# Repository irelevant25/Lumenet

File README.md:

# Lumenet

A lighting desk in the browser, in the old style with faders, and **dmxbox**: a small box that takes what the
desk sends over USB to the DMX512 cable of the lights.

## What it does

* **Faders for 1 to 8 universes** of 512 channels, a page at a time, and **128 memories**: looks stored from the
  faders, each with a fader of its own. Keys under the faders, independents at the side, a master, blackout,
  solo up and down, and a rate for everything that runs.
* **Several boxes at once**, each output playing a universe: by themselves, or as the project says. Besides
  the box, **Art-Net** nodes, **sACN** and DMX USB interfaces of the kind of the **Enttec DMX USB Pro** play the
  universes as well.
* **Sequences**, made by hand or from a template (chase, wave, strobe, fire, storm), and a **stack**: the cues
  of a show with their fades and waits, played one after the other with GO, or at moments of the music;
  a cue sheet to print.
* **Effects** worked out live from a shape: circles and swings of moving heads, chases and pulses, rainbows
  and color chases, and patterns over the cells of LED bars by where they are on the stage. Each has a key and
  a fader, live speed, size and spread, and a preview; on Main and in the stack too.
* **Sounds:** music and other sounds from files, mixed by the desk program and played on a sound device of the
  PC, each with a key and a fader, its own level in decibels, fades, pan, speed, pitch, echo and reverb; a
  volume for all, MUTE and LISTEN on a second device; in the stack and in sequences, where a sound can play on
  through the steps after it until its end or a release. Beside them the tracks of the USB stick of a
  Soundcraft Ui mixer, played on the mixer's own player, its PLAYER channel the volume of all sounds and MUTE,
  both ways; the desk finds the mixer in the network by itself.
* **Fixtures:** lights by their kind, taken from the Open Fixture Library (666 lights) or the library of QLC+
  (1,781), played by intensity and color, moving heads by pan and tilt too; groups with one fader for all their
  lights.
* **Stage:** a plan of the rig with every light in its live color, a strobe flashing too.
* **Projects** in files, with notes for the show, undo and redo, an autosave, and backups into a folder that
  Google Drive, OneDrive or Dropbox syncs; export and import as one ZIP, and import of the show files of
  theatre consoles (USITT ASCII).
* **Phones and tablets** in the same network can use the desk as well, with a password.
* **MIDI controllers** play the desk: their keys press its keys, their faders and knobs move its faders, and
  the desk lights their keys and moves their motorized faders. Learn maps a control in two presses; the Akai
  APC mini mk2, Korg nanoKONTROL2 and Behringer X-Touch Mini and Compact have ready-made mappings. Other
  programs such as QLab and TouchOSC work the same keys and faders with **OSC**.
* A keyboard shortcut for every key, the usual ones from the start, and settings for how each device shows
  the desk, with a setup by the kind of show on the first start.
* **Ten example shows** to start from, from a few looks and cues to a whole concert, one of effects, two of
  sounds and one whose cues come on the music.

The desk also works without the box, on other DMX hardware or none. The box speaks Art-Net too, so other
lighting software such as QLC+ can use it.

## What it runs on

**The desk** runs on Windows 10 and 11 (64-bit), and its page in a current browser. With LAN switched on in
the page, phones and tablets in the same network can use it too: they get the same page, laid out for their
screen, and get in with a password.

**The boxes:** four dmxboxes bring the desk to DMX. Each is a USB network adapter for the computer, which
Windows, macOS and Linux take without a driver, and the desk finds it by itself. One USB cable powers it and
carries the data.

| | <br>[**Box 1**](boxes/box1/README.md)<br>Pico | <br>[**Box 2**](boxes/box2/README.md)<br>PIC32 | <br>[**Box 3**](boxes/box3/README.md)<br>RP2040 | <br>[**Box 4**](boxes/box4/README.md)<br>RP2040 |
|---|:---:|:---:|:---:|:---:|
| Isolated DMX output | ✅ | ✅ | ✅ | ✅ |
| RDM: sets up the lights | ✅ | ✅ | ✅ | ✅ |
| Number switch, for several boxes | ✅ | ✅ | ✅ | ✅ |
| USB-C | ❌ | ✅ | ✅ | ✅ |
| DMX IN: a console plays the desk | ❌ | ❌ | ❌ | ✅ |
| MIDI IN and OUT | ❌ | ❌ | ❌ | ✅ |
| USB OUT to the next box | ❌ | ❌ | ❌ | ✅ |
| POWER socket for a charger | ❌ | ❌ | ❌ | ✅ |
| Update firmware over USB | ✅ | ❌ | ✅ | ✅ |
| Assembly | THT | THT | SMD | SMD |
| Soldered by external company | ❌ | ❌ | ✅ | ✅ |
| Case | 3D printed | 3D printed | 3D printed | Aluminium or 3D printed |

The pictures are renders of the designs; none of the four has been built yet. The first box 1, a
Raspberry Pi Pico on a perfboard, was built and works with the desk.

## Get it

**Download:** `Lumenet.exe` from the newest release on the [Releases](../../releases) page. It is the whole desk in
one file, with nothing to install. Start it: the page opens in the browser, and Lumenet sits in the
notification area of the taskbar, where its menu opens the page again, shows the log, and ends it. Windows may
say that it does not know the program, as it is not signed: More info, then Run anyway. Later versions come
from the desk itself: Settings, About, says when one is out and puts it in place at a press.

**From the sources:** with the .NET 10 SDK and Node.js 22, `run.cmd` starts the desk; then open
http://localhost:4200. `sim.cmd` starts a simulated box, Art-Net node, sACN receiver or USB interface for the
desk to play on, or a MIDI controller to play it with, without the hardware (see
[DEV.md](DEV.md#simulated-devices-simcmd)).

**A box:** what to order and what to buy and fit yourself is in each box's BOM.md, for example
[box 4's](boxes/box4/BOM.md); the schematics, the boards and the firmware are in [DEV.md](DEV.md#1-hardware), and
all four boxes in [boxes/](boxes/README.md).

## More

* [MANUAL.md](MANUAL.md): every view, key and setting of the desk.
* [DEV.md](DEV.md): the box's hardware and firmware, the PC side, how the desk is built and tested, the DX
  protocol, and what has been tried so far.

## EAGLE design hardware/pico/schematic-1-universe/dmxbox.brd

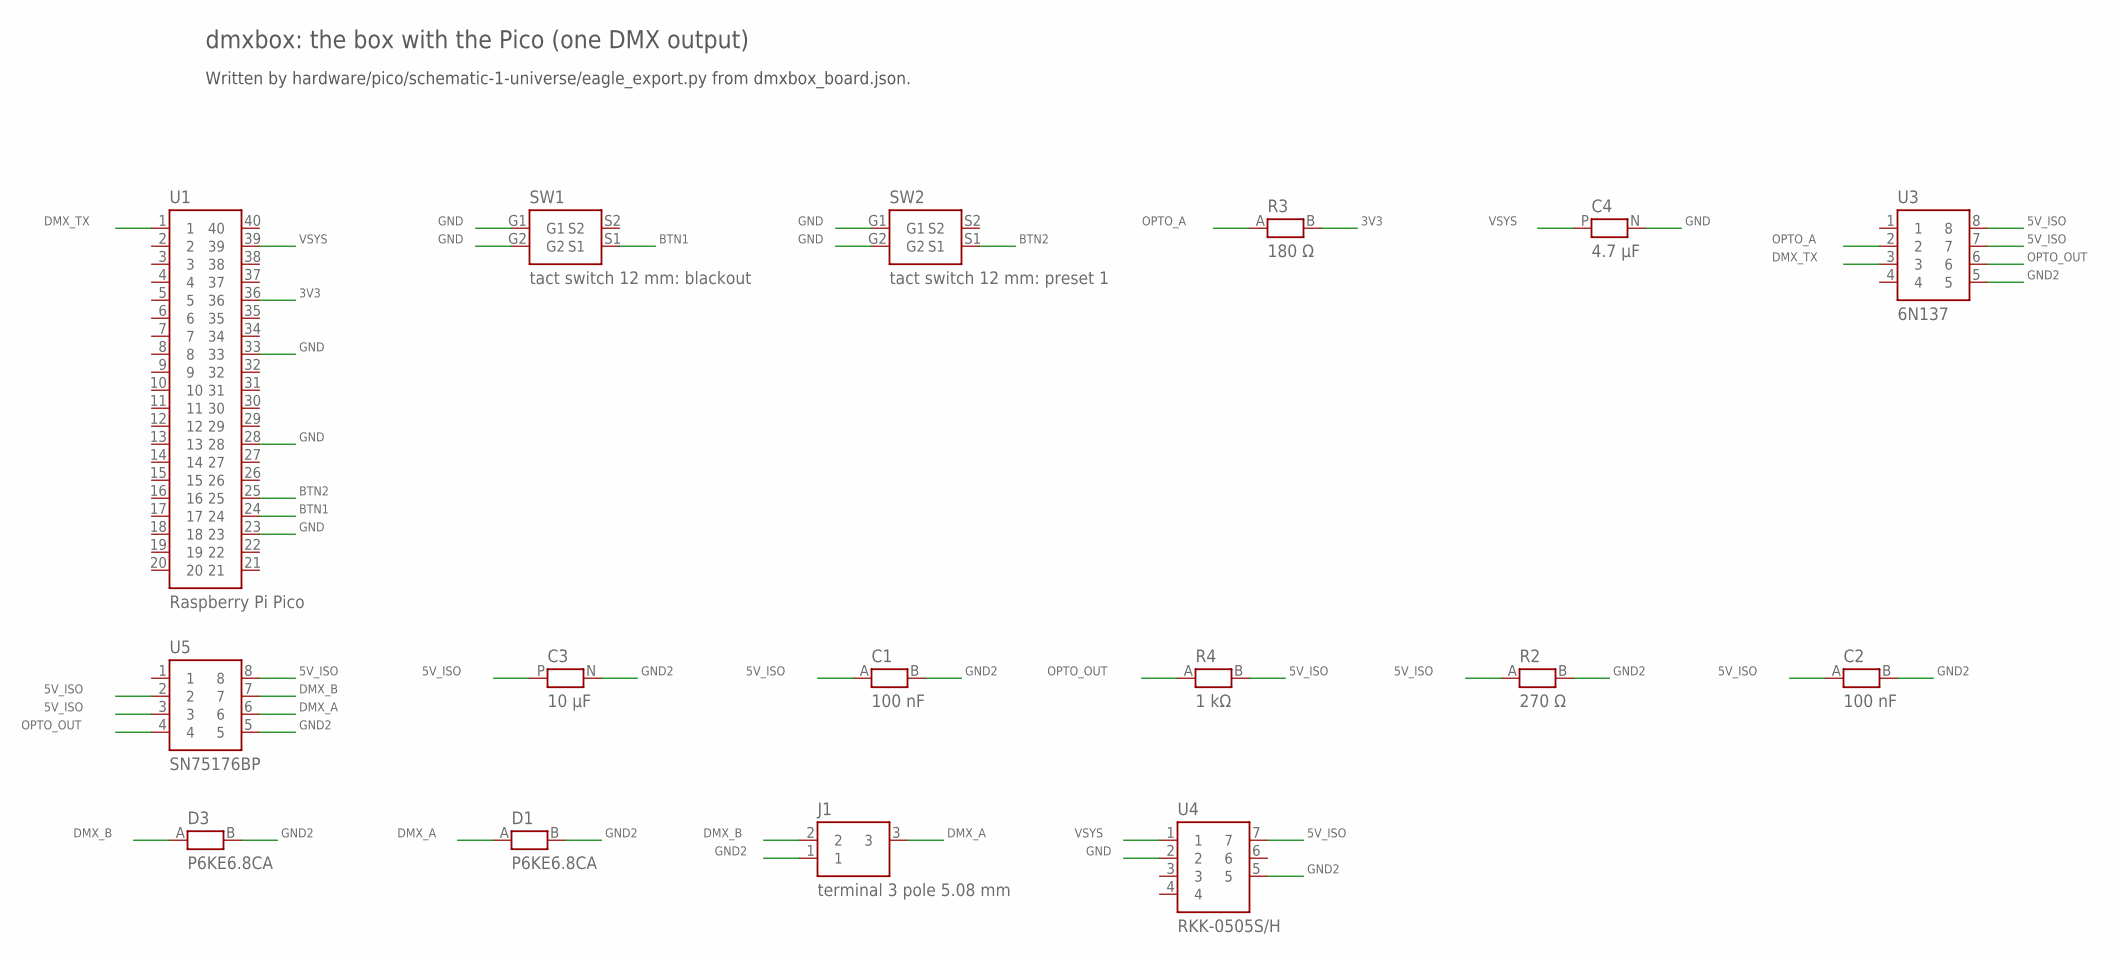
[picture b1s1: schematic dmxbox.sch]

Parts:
C1, C2: 100 nF; C_5.00
C3: 10 µF; CP_2.00
C4: 4.7 µF; CP_2.00
D1, D3: P6KE6.8CA; DO15_10.16
J1: terminal 3 pole 5.08 mm; TERMINAL_3
R2: 270 Ω; R_10.16
R3: 180 Ω; R_10.16
R4: 1 kΩ; R_10.16
SW1: tact switch 12 mm: blackout; BUTTON_12MM
SW2: tact switch 12 mm: preset 1; BUTTON_12MM
U1: Raspberry Pi Pico; PICO
U3: 6N137
U4: RKK-0505S/H; RKK_SIP7
U5: SN75176BP; SN75176

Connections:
3V3: R3.B, U1.36
5V_ISO: C1.A, C2.A, C3.P, R2.A, R4.B, U3.7, U3.8, U4.7, U5.2, U5.3, U5.8
BTN1: SW1.S1, U1.24
BTN2: SW2.S1, U1.25
DMX_A: D1.A, J1.3, U5.6
DMX_B: D3.A, J1.2, U5.7
DMX_TX: U1.1, U3.3
GND: C4.N, SW1.G1, SW1.G2, SW2.G1, SW2.G2, U1.23, U1.28, U1.33, U4.2
GND2: C1.B, C2.B, C3.N, D1.B, D3.B, J1.1, R2.B, U3.5, U4.5, U5.5
OPTO_A: R3.A, U3.2
OPTO_OUT: R4.A, U3.6, U5.4
VSYS: C4.P, U1.39, U4.1

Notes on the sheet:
dmxbox: the box with the Pico (one DMX output)
Written by hardware/pico/schematic-1-universe/eagle_export.py from dmxbox_board.json.

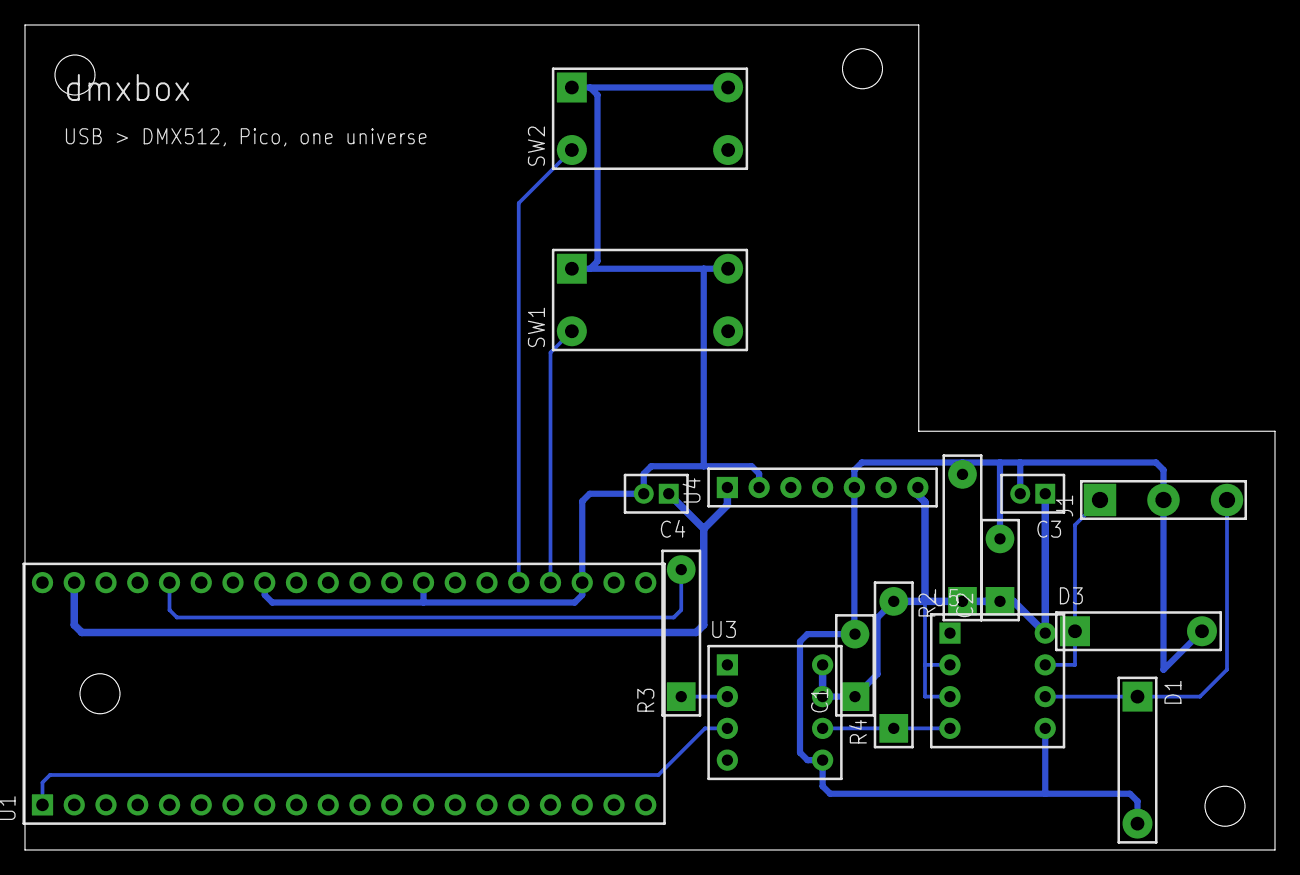
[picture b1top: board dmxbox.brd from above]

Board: 1 copper layer, 100.0 x 66.0 mm, 16 parts (0 on the bottom side), 12 nets.

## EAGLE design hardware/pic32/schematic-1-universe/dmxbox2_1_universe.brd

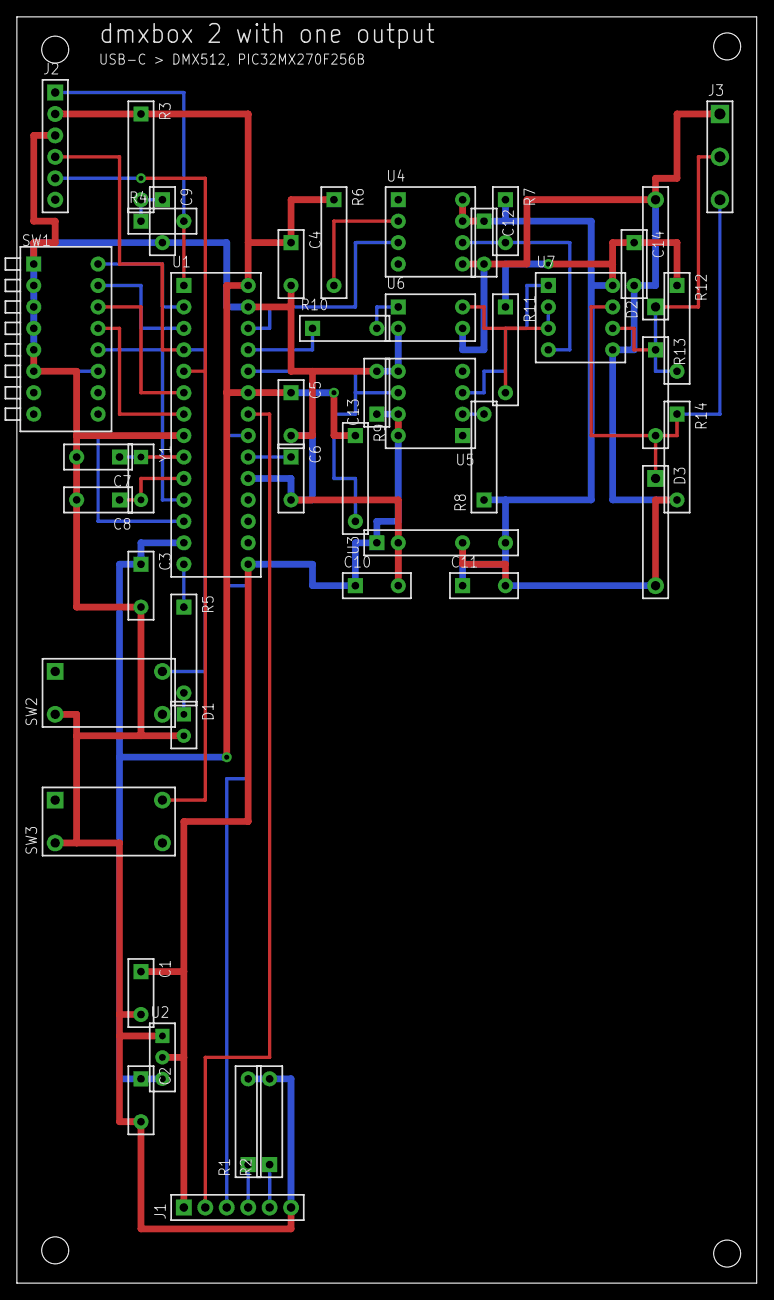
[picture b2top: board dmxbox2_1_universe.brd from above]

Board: 2 copper layers, 87.6 x 150.0 mm, 45 parts (0 on the bottom side), 35 nets.

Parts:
C1, C2, C6, C10, C11: 10 µF; C_5.08
C3, C4, C5, C9, C12, C13, C14: 100 nF; C_5.08
C7, C8: 22 pF; C_5.08
D1: LED 3 mm; LED_3MM
D2, D3: P6KE6.8CA; DO15_12.70
J1: USB 2.0 Type-C breakout; USB_C_BREAKOUT_1X6
J2: pin header 1x6; HEADER_1X6
J3: XLR 3-pin female, panel; TERMINAL_3_5.08
R1, R2: 5.1 kΩ; R_10.16
R3, R11: 10 kΩ; R_10.16
R4, R7: 1 kΩ; R_5.08_STANDING
R5: 470 Ω; R_10.16
R6: 180 Ω; R_10.16
R8: 390 Ω; R_10.16
R9: 1 kΩ; R_10.16
R10: 470 Ω; R_7.62
R12, R14: 560 Ω; R_10.16
R13: 130 Ω; R_10.16
SW1: piano DIP switch, 8 positions (DPL08RGT); PIANO_DIP_SWITCH_8
SW2, SW3: tact switch 12 x 12 mm; BUTTON_12MM
U1: PIC32MX270F256B-I/SP; PIC32MX270F256B_DIP28
U2: MCP1700-3302E/TO; MCP1700_TO92
U3: RKK-0505S/H; RKK0505SH_SIP7
U4, U5: 6N137; 6N137_DIP8
U6: PC817; PC817_DIP4
U7: MAX485; MAX485_DIP8
Y1: 8 MHz; HC49_CRYSTAL

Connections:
+3V3: C2.1, C3.1, C4.1, C5.1, J2.2, R3.1, R6.1, R9.1, U1.13, U1.23, U1.28, U2.3
+5V: C1.1, C10.1, C13.1, J1.VBUS, U1.15, U2.2, U3.1, U5.7, U5.8
+5V_ISO: C11.1, C12.1, C14.1, R7.1, R8.1, R11.1, R12.1, U3.7, U4.7, U4.8, U7.8
A1: D2.1, J3.3, R12.2, R13.1, U7.6
B1: D3.1, J3.2, R13.2, R14.1, U7.7
BLACKOUT: J2.4, SW2.net, U1.4
CC1: J1.CC1, R1.1
CC2: J1.CC2, R2.1
D+: J1.D+, U1.21
D-: J1.D-, U1.22
DE1: R11.2, U6.4, U7.2, U7.3
DI1: R7.2, U4.6, U7.4
DIR1: R10.1, U1.25
DIR1_LED: R10.2, U6.1
GND: C1.2, C2.2, C3.2, C4.2, C5.2, C6.2, C7.2, C8.2, C9.2, C10.2, C13.2, D1.K, J1.GND, J2.3, R1.2, R2.2, SW1.1, SW1.2, SW1.3, SW1.4, SW1.5, SW1.6, SW2.gnd, SW3.gnd, U1.8, U1.19, U1.27, U2.1, U3.2, U5.5, U6.2
GND2: C11.2, C12.2, C14.2, D2.2, D3.2, J3.1, R14.2, U3.5, U4.5, U6.3, U7.5
LED: R5.1, U1.14
LED_A: D1.A, R5.2
MCLR: J2.1, R4.2, U1.1
MCLR_RC: C9.1, R3.2, R4.1
N1: SW1.16, U1.2
N2: SW1.15, U1.3
N4: SW1.14, U1.6
N8: SW1.13, U1.7
N16: SW1.12, U1.11
N32: SW1.11, U1.12
OSC1: C7.1, U1.9, Y1.1
OSC2: C8.1, U1.10, Y1.2
PRESET: J2.5, SW3.net, U1.5
RO1: U5.3, U7.1
RO1_LED: R8.2, U5.2
RX1: R9.2, U1.24, U5.6
TX1: U1.26, U4.3
TX1_LED: R6.2, U4.2
VCAP: C6.1, U1.20

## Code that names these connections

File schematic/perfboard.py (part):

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
# Insulated wires on the parts side: net, from, to, color, what it is.
LINKS = [
    ("DMX_TX", "B1", "M4", "#7c3aed", "Pico pin 1 (GP0, the DMX data) to U3 pin 3"),
]

# Legs that belong to a net: the schematic's list, plus the button corners.
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EDGE_X, EDGE_Y = (BOARD_W - 25) / 2, (BOARD_H - 30) / 2   # from the board's edge to the first hole

NET_INFO = {                                              # color, what the net is
    "VSYS": ("#dc2626", "5 V from the USB cable (Pico pin 39)"),
    "GND": ("#111827", "ground of the Pico and the computer"),
    "3V3": ("#f59e0b", "3.3 V (Pico pin 36) to R3"),
    "LED_A": ("#ea580c", "R3 to U3 pin 2"),
    "DMX_TX": ("#7c3aed", "the DMX data: Pico pin 1 to U3 pin 3"),
    "BTN1": ("#0d9488", "button SW1, blackout (Pico pin 24)"),
    "BTN2": ("#65a30d", "button SW2, preset 1 (Pico pin 25)"),
    "+5V_ISO": ("#db2777", "isolated 5 V"),
    "GND2": ("#2563eb", "isolated ground, XLR pin 1"),
    "DI": ("#a21caf", "the DMX data: U3 pin 6 to U5 pin 4"),
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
